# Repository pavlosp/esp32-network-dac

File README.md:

# ESP32-based network streamer and DAC

## Description

This is my first attempt at a simple, high-quality Digital to Analog Converter (DAC) and network streamer. Design is based around the ESP32 WiFi microcontroller, with a Texas Instruments PCM5122 high-quality DAC.

Schematic and PCB layout designed on KiCad 6.

## Schematic and PCB

Manufacturing files are included for the first iteration of the circuit board.

## Next steps

Refine component selection to simpler components for easier assembly (C0G capacitors).

Longer-term plan: Build on this design to build digital mixer and USB audio interface (potentially with different microcontroller from STM32 range)

## Acknowledgements

Thanks to all the online resources and reference DAC implementations (on TI data sheets). The design can be further improved of course - any suggestions, do let me know.

Many thanks to the [squeezelite-esp32](https://github.com/sle118/squeezelite-esp32) project for the software stack, which includes AirPlay and works with some configuration changes - I2S pinout configuration for digital audio data and clock signals.

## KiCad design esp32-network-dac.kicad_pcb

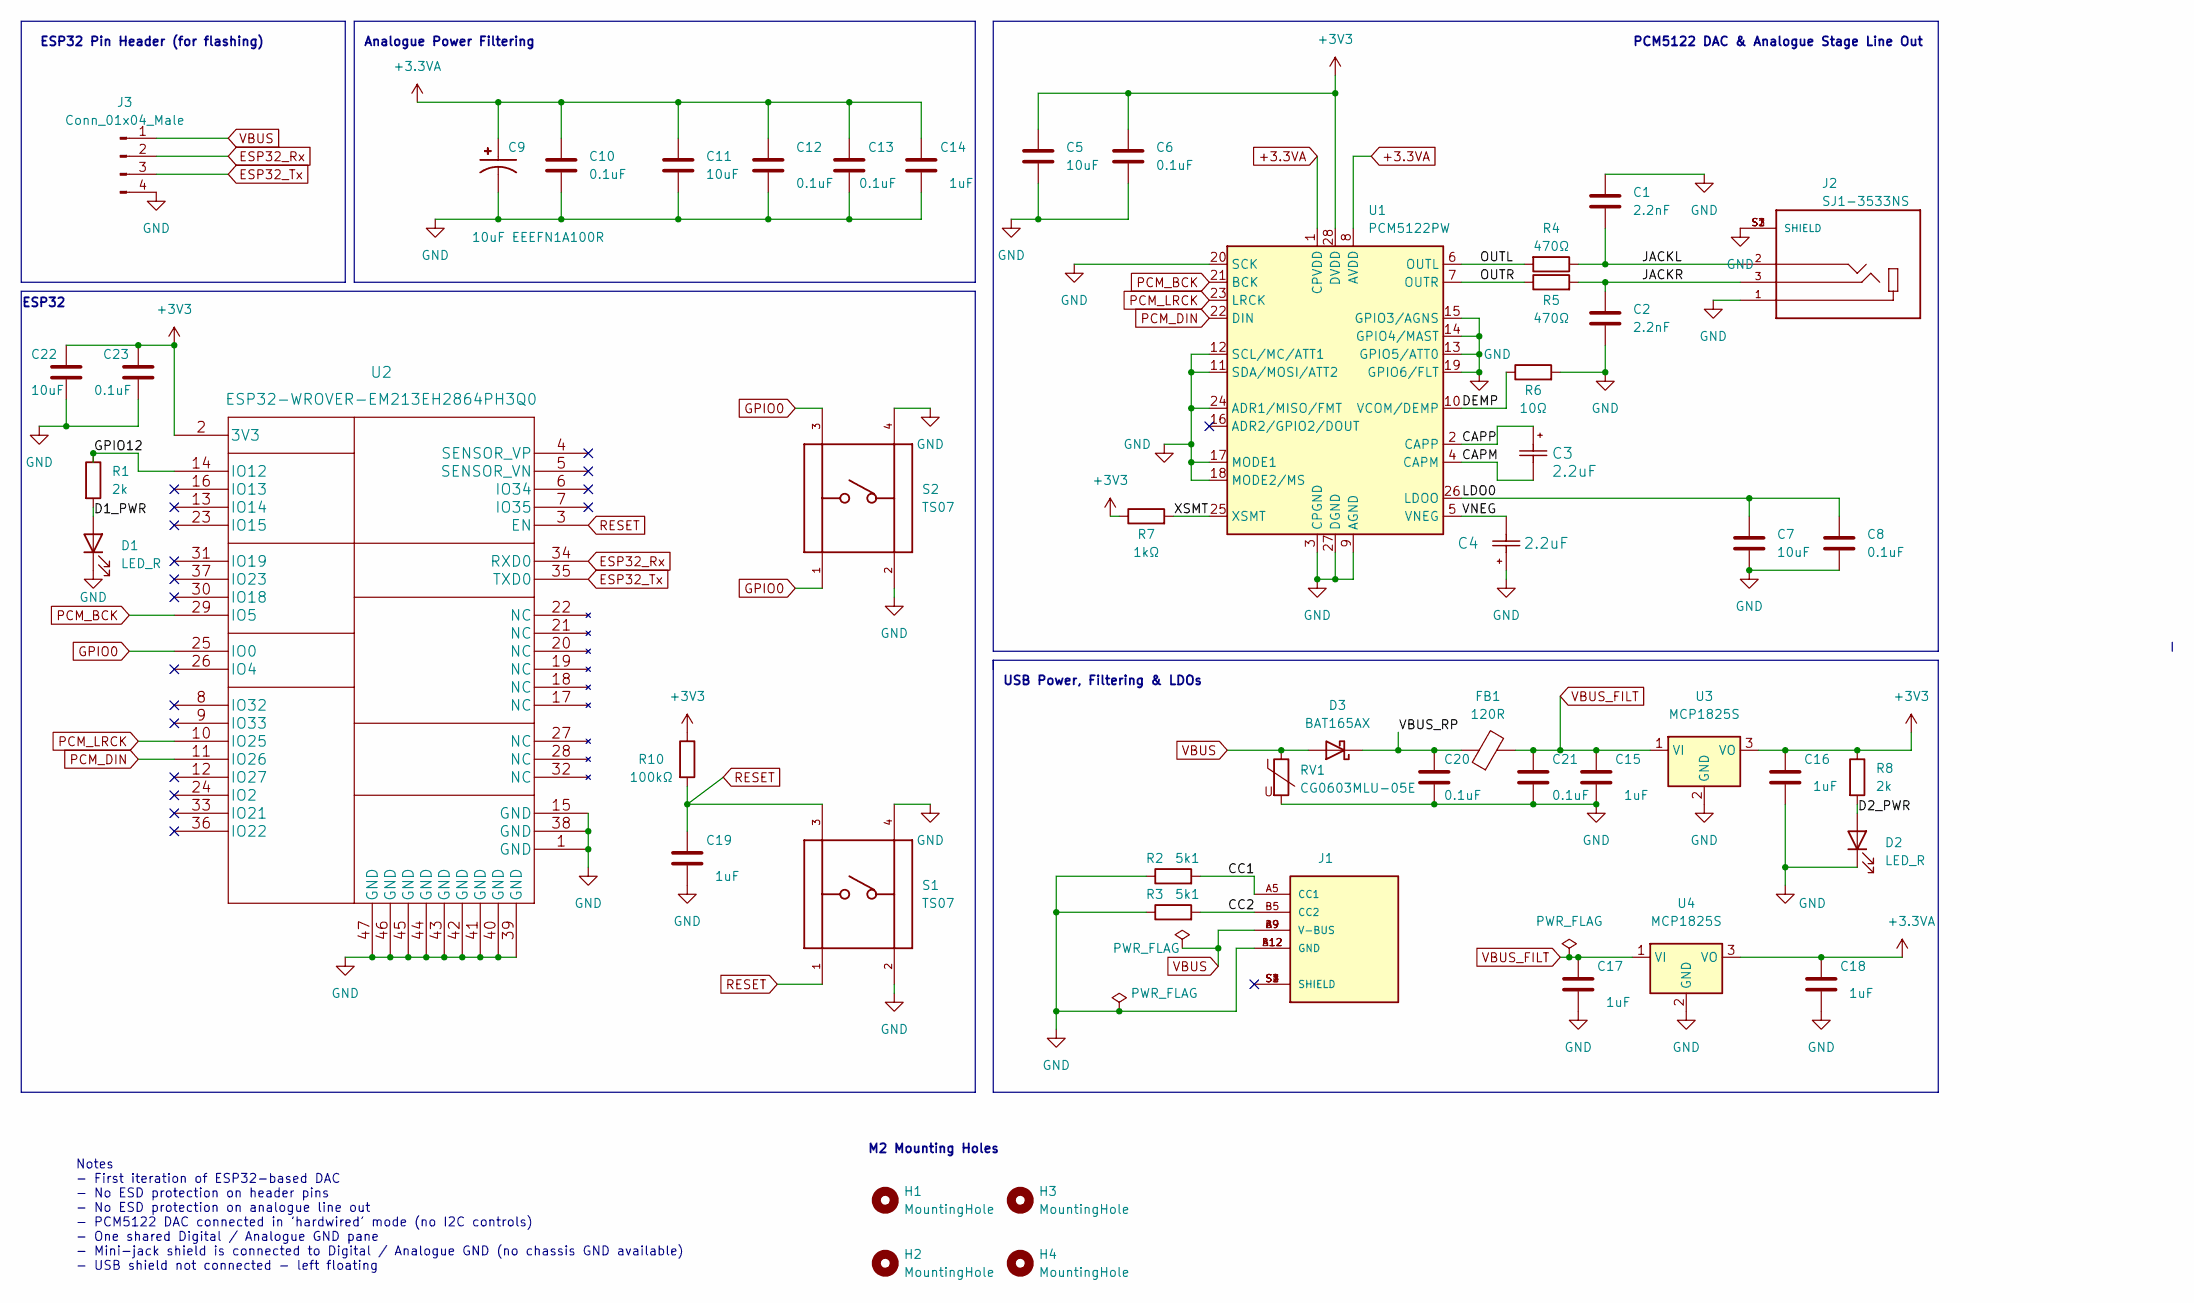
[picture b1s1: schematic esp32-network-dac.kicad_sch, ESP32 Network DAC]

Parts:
C1, C2: 2.2nF; C_0805_2012Metric
C3, C4: 2.2uF; UUQ1H2R2MCL1GB
C5, C11, C22: 10uF; C_1206_3216Metric
C6, C8, C10, C12, C13, C20, C21, C23: 0.1uF; C_0805_2012Metric
C7: 10uF; C_0805_2012Metric
C9: 10uF EEEFN1A100R; CAP_EEEFN1A100R; PARTREV 10-Oct-19
C14, C15, C16, C17, C18, C19: 1uF; C_0603_1608Metric
D1, D2: LED_R; LED_0603_1608Metric
D3: BAT165AX; D_SOD-323
FB1: 120R; R_0603_1608Metric
H1, H2, H3, H4: MountingHole; MountingHole_2.2mm_M2
J1: UJC-HP-3-SMT-TR; CUI_UJC-HP-3-SMT-TR; PARTREV 04/30/2020
J2: SJ1-3533NS; CUI_SJ1-3533NS
J3: Conn_01x04_Male; PinHeader_1x04_P2.54mm_Vertical
R1, R8: 2k; R_0603_1608Metric
R2, R3: 5k1; R_0603_1608Metric
R4, R5: 470Ω; R_0603_1608Metric
R6: 10Ω; R_0603_1608Metric
R7: 1kΩ; R_0603_1608Metric
R10: 100kΩ; R_0603_1608Metric
RV1: CG0603MLU-05E; R_0603_1608Metric
S1, S2: TS07; SW_TS07-667-37-BK-260-SMT-TR; PARTREV 1.0
U1: PCM5122PW; TSSOP-28_4.4x9.7mm_P0.65mm
U2: ESP32-WROVER-EM213EH2864PH3Q0
U3, U4: MCP1825S; SOT-223-3_TabPin2

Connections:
+3.3VA: C9.1, C10.1, C11.1, C12.1, C13.1, C14.1, C18.1, U1.1 (CPVDD), U1.8 (AVDD), U4.3 (VO)
+3V3: C5.1, C6.1, C16.1, C22.1, C23.1, R7.1, R8.1, R10.1, U1.28 (DVDD), U2.2 (3V3), U3.3 (VO)
/CAPM: C3.2, U1.4 (CAPM)
/CAPP: C3.1, U1.2 (CAPP)
/CC1: J1.A5 (CC1), R2.2
/CC2: J1.B5 (CC2), R3.2
/D1_PWR: D1.2 (A), R1.2
/D2_PWR: D2.2 (A), R8.2
/DEMP: R6.1, U1.10 (VCOM/DEMP)
/GPIO12: R1.1, U2.14 (IO12)
/JACKL: C1.2, J2.2, R4.1
/JACKR: C2.1, J2.3, R5.2
/LDO0: C7.1, C8.1, U1.26 (LDOO)
/OUTL: R4.2, U1.6 (OUTL)
/OUTR: R5.1, U1.7 (OUTR)
/VBUS_RP: C20.1, D3.1 (K), FB1.1
/VNEG: C4.2, U1.5 (VNEG)
/XSMT: R7.2, U1.25 (XSMT)
ESP32_Rx: J3.2, U2.34 (RXD0)
ESP32_Tx: J3.3, U2.35 (TXD0)
GND: C1.1, C2.2, C4.1, C5.2, C6.2, C7.2, C8.2, C9.2, C10.2, C11.2, C12.2, C13.2, C14.2, C15.2, C16.2, C17.2, C18.2, C19.2, C20.2, C21.2, C22.2, C23.2, D1.1 (K), D2.1 (K), J1.A12 (GND), J1.B12 (GND), J2.1, J2.S1 (SHIELD), J2.S2 (SHIELD), J2.S3 (SHIELD), J3.4, R2.1, R3.1, R6.2, RV1.2, S1.2, S1.4, S2.2, S2.4, U1.3 (CPGND), U1.9 (AGND), U1.11 (SDA/MOSI/ATT2), U1.12 (SCL/MC/ATT1), U1.13 (GPIO5/ATT0), U1.14 (GPIO4/MAST), U1.15 (GPIO3/AGNS), U1.17 (MODE1), U1.18 (MODE2/MS), U1.19 (GPIO6/FLT), U1.20 (SCK), U1.24 (ADR1/MISO/FMT), U1.27 (DGND), U2.1 (GND), U2.15 (GND), U2.38 (GND), U2.39 (GND), U2.40 (GND), U2.41 (GND), U2.42 (GND), U2.43 (GND), U2.44 (GND), U2.45 (GND), U2.46 (GND), U2.47 (GND), U3.2 (GND), U4.2 (GND)
GPIO0: S2.1, S2.3, U2.25 (IO0)
PCM_BCK: U1.21 (BCK), U2.29 (IO5)
PCM_DIN: U1.22 (DIN), U2.11 (IO26)
PCM_LRCK: U1.23 (LRCK), U2.10 (IO25)
RESET: C19.1, R10.2, S1.1, S1.3, U2.3 (EN)
VBUS: D3.2 (A), J1.A9 (V-BUS), J1.B9 (V-BUS), J3.1, RV1.1
VBUS_FILT: C15.1, C17.1, C21.1, FB1.2, U3.1 (VI), U4.1 (VI)

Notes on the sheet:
ESP32 Pin Header (for flashing)
M2 Mounting Holes
Notes - First iteration of ESP32-based DAC - No ESD protection on header pins - No ESD protection on analogue line out - PCM5122 DAC connected in 'hardwired' mode (no I2C controls) - One shared Digital / Analogue GND pane - Mini-jack shield is connected to Digital / Analogue GND (no chassis GND ava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
USB Power, Filtering & LDOs
Analogue Power Filtering
PCM5122 DAC & Analogue Stage Line Out
ESP32

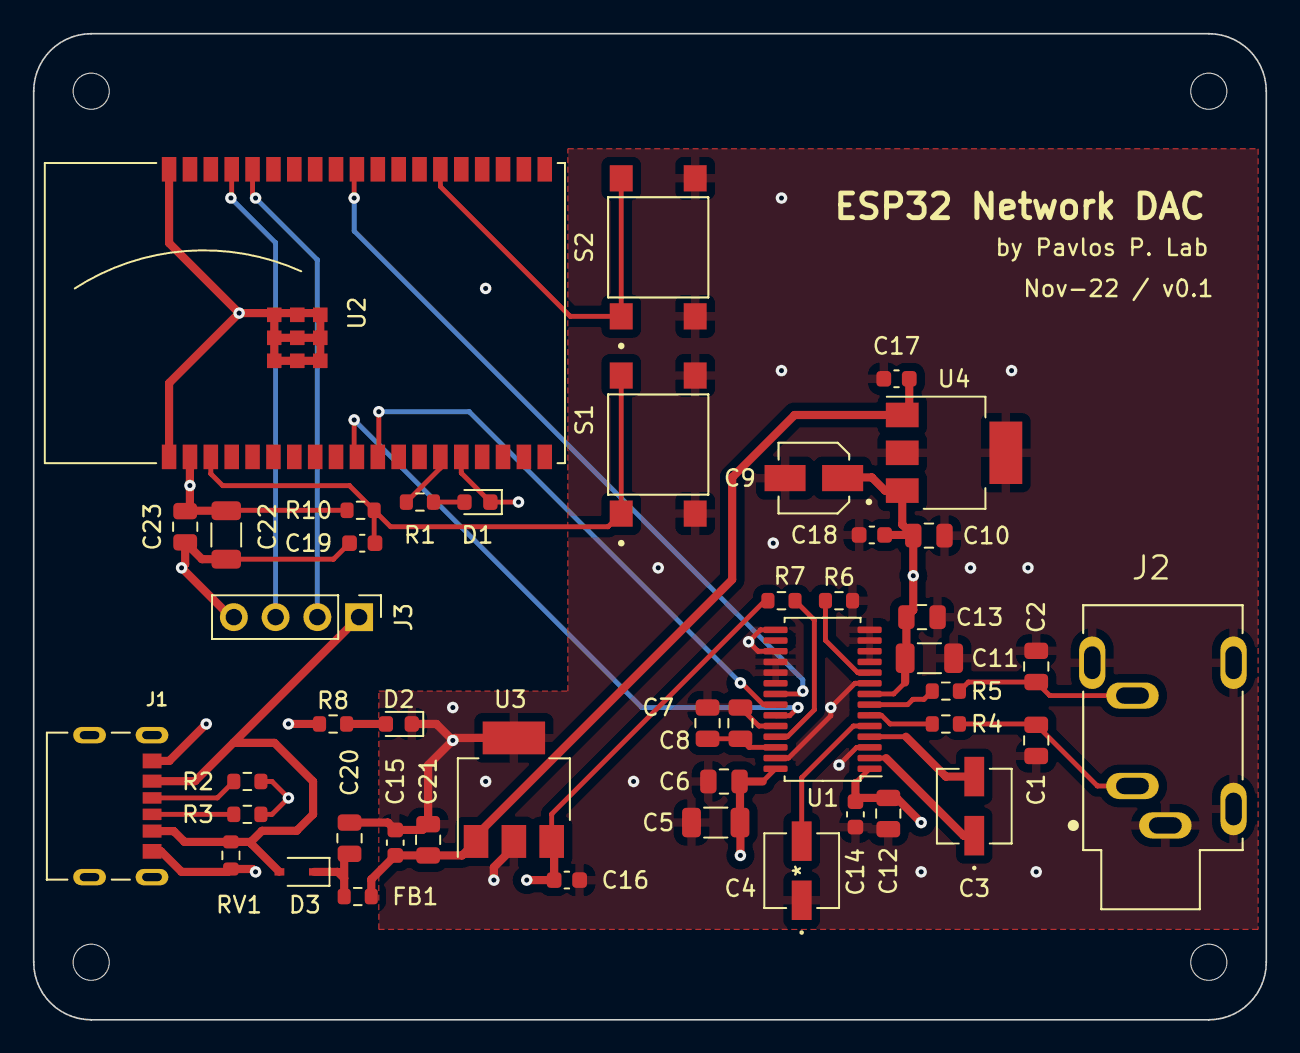
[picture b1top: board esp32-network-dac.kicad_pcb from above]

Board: 4 copper layers, 75.0 x 60.0 mm, 50 parts (0 on the bottom side), 28 nets.

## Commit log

2022-03-27 Adding README
2022-03-27 Removing .DS_Store
2022-04-03 latest commit
2022-04-13 added a few backups
2022-05-12 removed backups and started changes on USB recepticle
2022-07-10 deleted .DS_Store
2022-08-07 minor update on text label TODO
2022-11-05 Added new LDO, USB connector and ESD protection on USB power line
2022-11-05 Updates to schematic - nearly complete
2022-11-06 Updates and fixes based on ERC checks
2022-11-06 Added PCB first iteration - placed components in a logical layout
2022-11-06 Added more traces and a ground plane
2022-11-07 Continued working on PCB - most traces laid out. Need to adhere to DRC rules though
2022-11-08 Fixes to footprints and added more traces. Need to fix all DRC errors & warnings next.
2022-11-12 Sensible changes to grid and component placement for DAC (following TI datasheet)
2022-11-12 Analog DAC components now laid out properly (hopefully).
2022-11-12 Updated PCB layout - now it looks cleaner - completed layout. next step: traces
2022-11-12 Updated name to ESP32 Network DAC (local KiCad files and github)
2022-11-13 Updates to PCB - traces all done and most ground planes etc.
2022-11-13 Changed footrpints to remove DRC warnings. Added board outline.
2022-11-14 Updates to USB C receptive - replaced mid-mount recepticle with SMT
2022-11-20 Finalised v0.1 design and created manufacturing files
2024-03-11 Added schematic and PCB board picture on README

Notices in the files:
parts and their libraries:
Copyright 2021 Accelerated Designs. All rights reserved.
